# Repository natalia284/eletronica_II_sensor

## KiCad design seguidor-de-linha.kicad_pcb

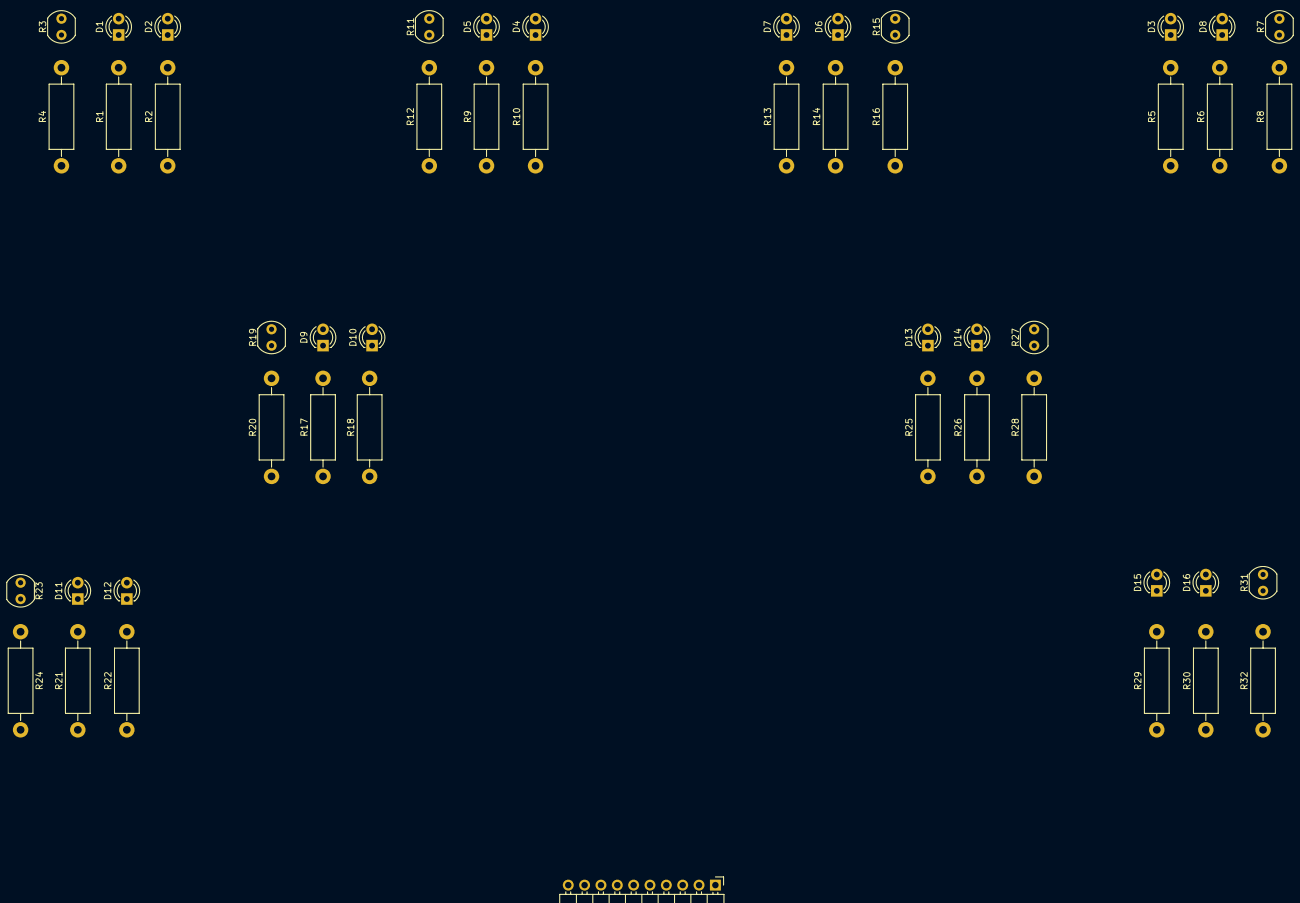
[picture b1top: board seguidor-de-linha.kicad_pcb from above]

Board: 2 copper layers, 49 parts (0 on the bottom side), 33 nets, no tracks yet.

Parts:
D1, D3, D5, D7, D9, D11, D13, D15: IR204A; LED_D3.0mm_IRBlack
D2, D4, D6, D8, D10, D12, D14, D16: BPW21; LED_D3.0mm_IRBlack
J2: Conn_01x10; PinHeader_1x10_P2.54mm_Horizontal
R1, R2, R4, R5, R6, R8, R9, R10, R12, R13, R14, R16, R17, R18, R20, R21, R22, R24, R25, R26, R28, R29, R30, R32: R_US; R_Axial_DIN0411_L9.9mm_D3.6mm_P15.24mm_Horizontal
R3, R7, R11, R15, R19, R23, R27, R31: VT93xx; R_LDR_4.9x4.2mm_P2.54mm_Vertical

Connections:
5V: J2.9, R1.1, R2.1, R3.1, R5.1, R6.1, R7.1, R9.1, R10.1, R11.1, R13.1, R14.1, R15.1, R17.1, R18.1, R19.1, R21.1, R22.1, R23.1, R25.1, R26.1, R27.1, R29.1, R30.1, R31.1
GND: D1.1 (K), D3.1 (K), D5.1 (K), D7.1 (K), D9.1 (K), D10.1 (A), D11.1 (K), D13.1 (K), D15.1 (K), J2.10, R4.2, R8.2, R12.2, R16.2, R20.2, R24.2, R28.2, R32.2
unnamed: D1.2 (A), R1.2
unnamed: D2.2 (K), R2.2
unnamed: D3.2 (A), R5.2
unnamed: D4.2 (K), R10.2
unnamed: D5.2 (A), R9.2
unnamed: D6.2 (K), R14.2
unnamed: D7.2 (A), R13.2
unnamed: D8.2 (K), R6.2
unnamed: D9.2 (A), R17.2
unnamed: D11.2 (A), R21.2
unnamed: D12.2 (K), R22.2
unnamed: D13.2 (A), R25.2
unnamed: D14.2 (K), R26.2
unnamed: D15.2 (A), R29.2
unnamed: D16.2 (K), R30.2
unnamed: R3.2, R4.1
unnamed: R7.2, R8.1
unnamed: R11.2, R12.1
unnamed: R15.2, R16.1
unnamed: R19.2, R20.1
unnamed: R23.2, R24.1
unnamed: R27.2, R28.1
unnamed: R31.2, R32.1
S1: D12.1 (A), J2.1
S2: D10.2 (K), J2.2
S3: D4.1 (A), J2.3
S4: D6.1 (A), J2.4
S5: D14.1 (A), J2.5
S6: D16.1 (A), J2.6
S7: D2.1 (A), J2.7
S8: D8.1 (A), J2.8
